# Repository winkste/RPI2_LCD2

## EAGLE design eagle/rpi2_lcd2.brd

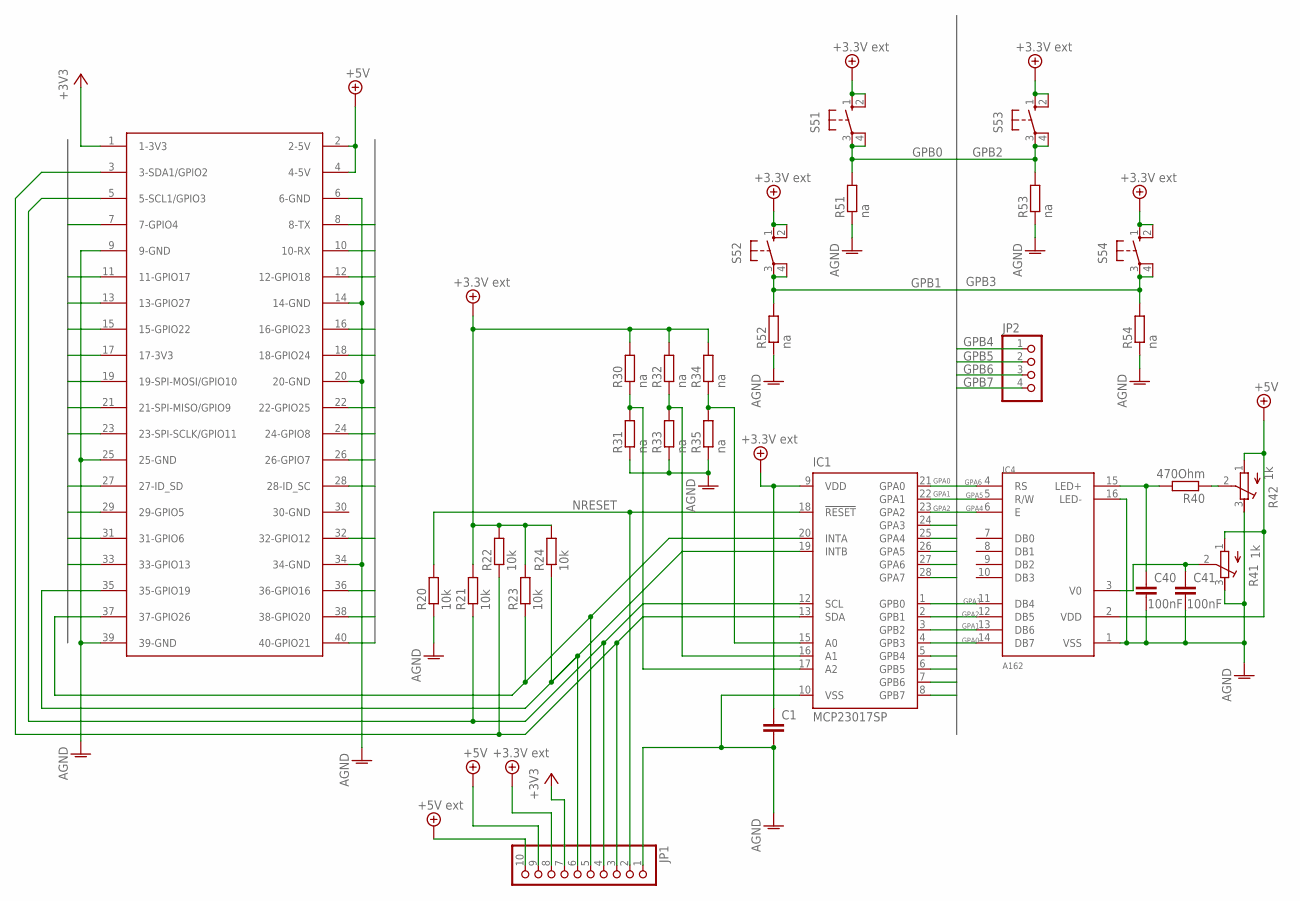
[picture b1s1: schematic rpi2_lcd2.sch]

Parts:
C1: C-EUC1210; C1210
C40, C41: 100nF; C1210
IC1: MCP23017SP; DIL28-3
IC4: A162
JP1: PINHD-1X10; 1X10
JP2: PINHD-1X4; 1X04
R20, R21, R22, R23, R24: 10k; R0805
R30, R31, R32, R33, R34, R35, R51, R52, R53, R54: na; R0805
R40: 470Ohm; R0805
R41, R42: 1k; RTRIM3339P
S51, S52, S53, S54: 10-XX; B3F-10XX
U$1: RASPBERRY-PI+HEADERONLY; RASPBERRY-PI-PLUS-HEADERONLY

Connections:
3.3VEXT: C1.1, IC1.9 (VDD), JP1.8, R21.2, R22.2, R23.2, R24.2, R30.2, R32.2, R34.2
+3V3: JP1.7, U$1.1 (1-3V3)
+5V: IC4.2 (VDD), JP1.9, R41.1 (A), R42.1 (A), U$1.2 (2-5V), U$1.4 (4-5V)
+5V/1: JP1.10
+5V/2: S51.1 (S), S51.2 (S1), S52.1 (S), S52.2 (S1), S53.1 (S), S53.2 (S1), S54.1 (S), S54.2 (S1)
AGND: C1.2, C40.2, C41.2, IC1.10 (VSS), IC4.1 (VSS), IC4.16 (LED-), JP1.1, R20.1, R31.1, R33.1, R35.1, R41.3 (E), R42.3 (E), R51.1, R52.1, R53.1, R54.1, U$1.6 (6-GND), U$1.9 (9-GND), U$1.14 (14-GND), U$1.20 (20-GND), U$1.25 (25-GND), U$1.34 (34-GND), U$1.39 (39-GND)
GPA0: IC1.21 (GPA0), IC4.14 (DB7)
GPA1: IC1.22 (GPA1), IC4.13 (DB6)
GPA2: IC1.23 (GPA2), IC4.12 (DB5)
GPA3: IC1.24 (GPA3), IC4.11 (DB4)
GPA4: IC1.25 (GPA4), IC4.6 (E)
GPA5: IC1.26 (GPA5), IC4.5 (R/W)
GPA6: IC1.27 (GPA6), IC4.4 (RS)
GPA7: IC1.28 (GPA7)
GPB0: IC1.1 (GPB0), R51.2, S51.3, S51.4 (P1)
GPB1: IC1.2 (GPB1), R52.2, S52.3, S52.4 (P1)
GPB2: IC1.3 (GPB2), R53.2, S53.3, S53.4 (P1)
GPB3: IC1.4 (GPB3), R54.2, S54.3, S54.4 (P1)
GPB4: IC1.5 (GPB4), JP2.1
GPB5: IC1.6 (GPB5), JP2.2
GPB6: IC1.7 (GPB6), JP2.3
GPB7: IC1.8 (GPB7), JP2.4
GPIO3: IC1.13 (SDA), JP1.3, R22.1, U$1.3 (3-SDA1/GPIO2)
GPIO5: IC1.12 (SCL), JP1.4, R21.1, U$1.5 (5-SCL1/GPIO3)
GPIO7: U$1.7 (7-GPIO4)
GPIO8: U$1.8 (8-TX)
GPIO10: U$1.10 (10-RX)
GPIO11: U$1.11 (11-GPIO17)
GPIO12: U$1.12 (12-GPIO18)
GPIO13: U$1.13 (13-GPIO27)
GPIO15: U$1.15 (15-GPIO22)
GPIO16: U$1.16 (16-GPIO23)
GPIO17: U$1.17 (17-3V3)
GPIO18: U$1.18 (18-GPIO24)
GPIO19: U$1.19 (19-SPI-MOSI/GPIO10)
GPIO21: U$1.21 (21-SPI-MISO/GPIO9)
GPIO22: U$1.22 (22-GPIO25)
GPIO23: U$1.23 (23-SPI-SCLK/GPIO11)
GPIO24: U$1.24 (24-GPIO8)
GPIO26: U$1.26 (26-GPIO7)
GPIO27: U$1.27 (27-ID_SD)
GPIO28: U$1.28 (28-ID_SC)
GPIO29: U$1.29 (29-GPIO5)
GPIO31: U$1.31 (31-GPIO6)
GPIO32: U$1.32 (32-GPIO12)
GPIO33: U$1.33 (33-GPIO13)
GPIO35: IC1.19 (INTB), JP1.6, R24.1, U$1.35 (35-GPIO19)
GPIO36: U$1.36 (36-GPIO16)
GPIO37: IC1.20 (INTA), JP1.5, R23.1, U$1.37 (37-GPIO26)
GPIO38: U$1.38 (38-GPIO20)
GPIO40: U$1.40 (40-GPIO21)
unnamed: R40.1, R42.2 (S)
unnamed: C40.1, IC4.15 (LED+), R40.2
unnamed: C41.1, IC4.3 (V0), R41.2 (S)
unnamed: IC1.17 (A2), R30.1, R31.2
unnamed: IC1.16 (A1), R32.1, R33.2
unnamed: IC1.15 (A0), R34.1, R35.2
NRESET: IC1.18 (!RESET), JP1.2, R20.2

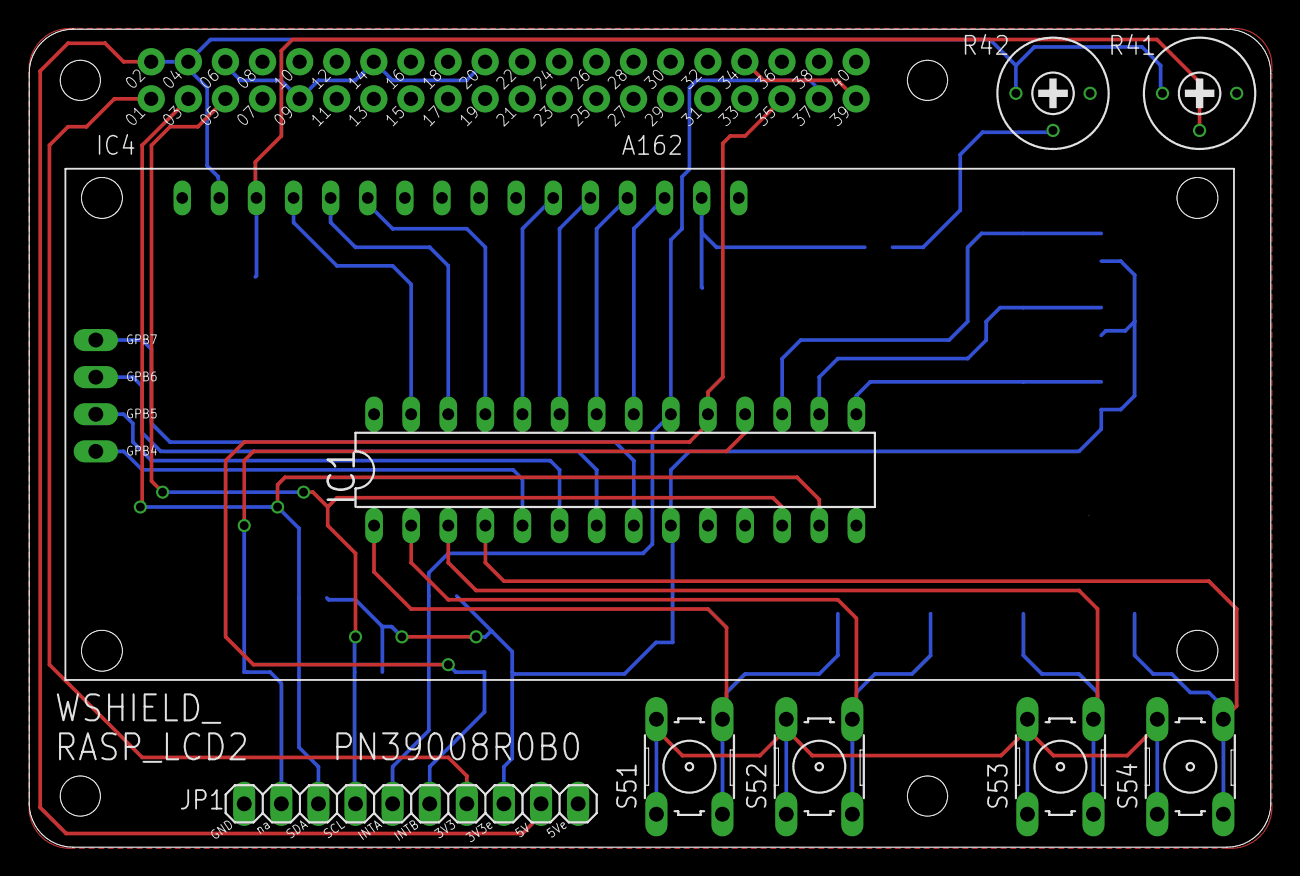
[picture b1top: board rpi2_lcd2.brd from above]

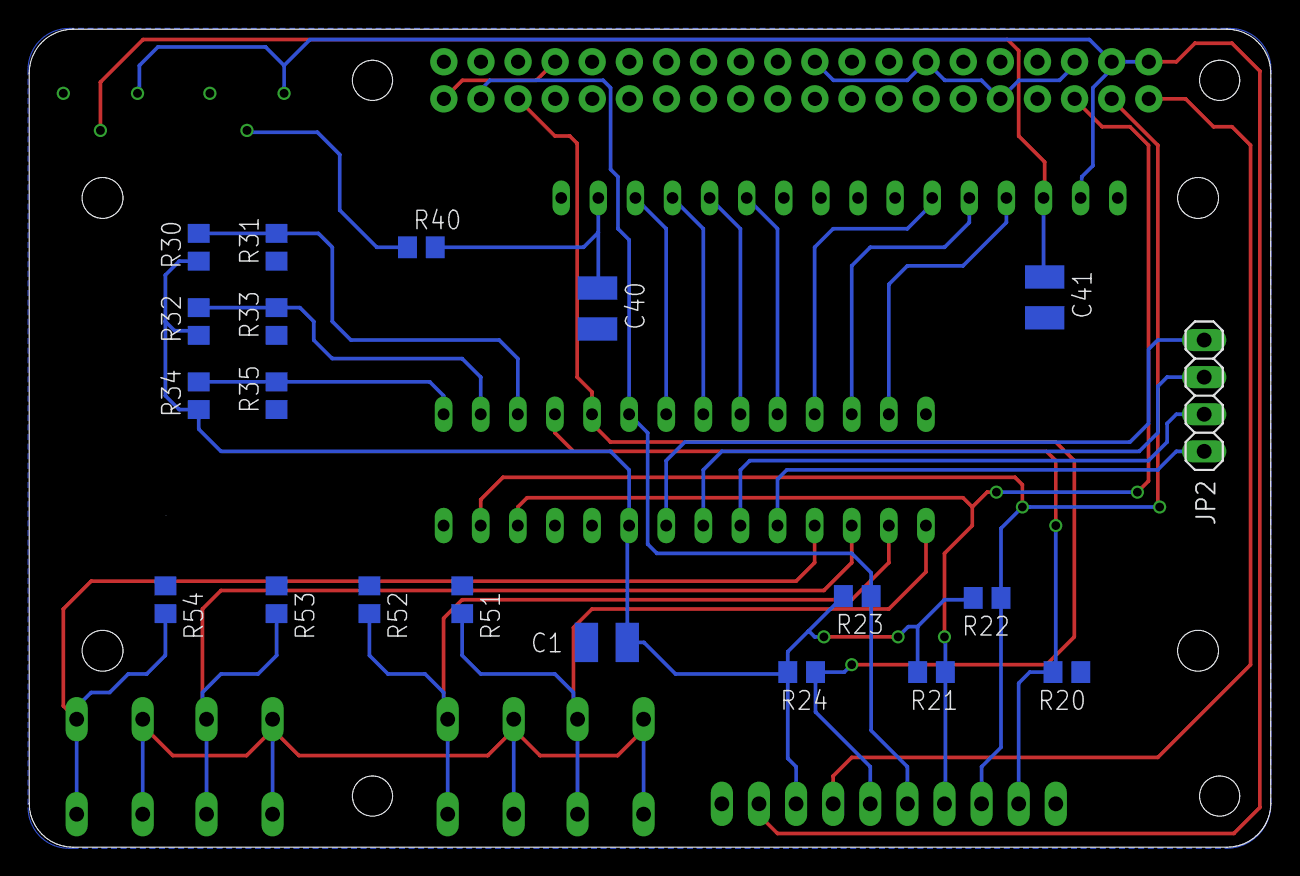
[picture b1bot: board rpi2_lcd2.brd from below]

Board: 2 copper layers, 85.0 x 56.0 mm, 32 parts (21 on the bottom side), 31 nets.

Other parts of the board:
U$2, U$3: BRAND_SWI

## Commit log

2017-03-25 initial project version
